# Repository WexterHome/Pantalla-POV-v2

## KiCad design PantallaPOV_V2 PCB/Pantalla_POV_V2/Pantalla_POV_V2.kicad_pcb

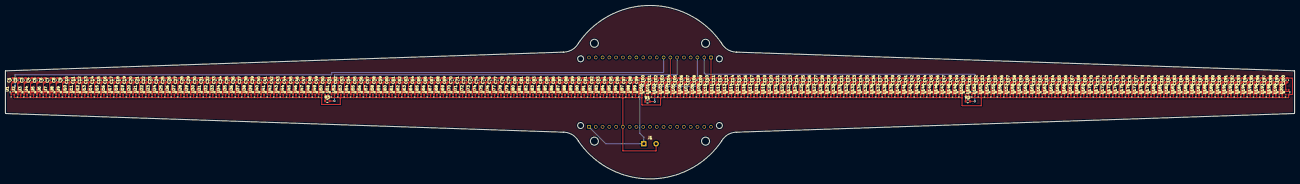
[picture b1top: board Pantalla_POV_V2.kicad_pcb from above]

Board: 2 copper layers, 483.1 x 65.0 mm, 405 parts (1 on the bottom side), 205 nets.

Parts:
C1, C2, C3, C4, C5, C6, C7, C8, C9, C10, C11, C12, C13, C14, C15, C16, C17, C18, C19, C20, C21, C22, C23, C24, C25, C26, C27, C28, C29, C30, C31, C32, C33, C34, C35, C36, C37, C38, C39, C40, C41, C42, C43, C44, C45, C46, C47, C48, C49, C50, C51, C52, C53, C54, C55, C56, C57, C58, C59, C60, C61, C62, C63, C64, C65, C66, C67, C68, C69, C70, C71, C72, C73, C74, C75, C76, C77, C78, C79, C80, C81, C82, C83, C84, C85, C86, C87, C88, C89, C90, C91, C92, C93, C94, C95, C96, C97, C98, C99, C100, C101, C102, C103, C104, C105, C106, C107, C108, C109, C110, C111, C112, C113, C114, C115, C116, C117, C118, C119, C120, C121, C122, C123, C124, C125, C126, C127, C128, C129, C130, C131, C132, C133, C134, C135, C136, C137, C138, C139, C140, C141, C142, C143, C144, C145, C146, C147, C148, C149, C150, C151, C152, C153, C154, C155, C156, C157, C158, C159, C160, C161, C162, C163, C164, C165, C166, C167, C168, C169, C170, C171, C172, C173, C174, C175, C176, C177, C178, C179, C180, C181, C182, C183, C184, C185, C186, C187, C188, C189, C190, C191, C192, C193, C194, C195, C196, C197, C198, C199, C200: C; C_0603_1608Metric
J1: Conn_01x02_Female; SolderWire-0.5sqmm_1x02_P4.6mm_D0.9mm_OD2.1mm
R1, R2, R3: 0; R_0603_1608Metric
U1, U2, U3, U4, U5, U6, U7, U8, U9, U10, U11, U12, U13, U14, U15, U16, U17, U18, U19, U20, U21, U22, U23, U24, U25, U26, U27, U28, U29, U30, U31, U32, U33, U34, U35, U36, U37, U38, U39, U40, U41, U42, U43, U44, U45, U46, U47, U48, U49, U50, U51, U52, U53, U54, U55, U56, U57, U58, U59, U60, U61, U62, U63, U64, U65, U66, U67, U68, U69, U70, U71, U72, U73, U74, U75, U76, U77, U78, U79, U80, U81, U82, U83, U84, U85, U86, U87, U88, U89, U90, U91, U92, U93, U94, U95, U96, U97, U98, U99, U100, U101, U102, U103, U104, U105, U106, U107, U108, U109, U110, U111, U112, U113, U114, U115, U116, U117, U118, U119, U120, U121, U122, U123, U124, U125, U126, U127, U128, U129, U130, U131, U132, U133, U134, U135, U136, U137, U138, U139, U140, U141, U142, U143, U144, U145, U146, U147, U148, U149, U150, U151, U152, U153, U154, U155, U156, U157, U158, U159, U160, U161, U162, U163, U164, U165, U166, U167, U168, U169, U170, U171, U172, U173, U174, U175, U176, U177, U178, U179, U180, U181, U182, U183, U184, U185, U186, U187, U188, U189, U190, U191, U192, U193, U194, U195, U196, U197, U198, U199, U200: WS2812-2020; LED_WS2812-2020
U201: ESP32_NODEMCU; MODULE_ESP32_NODEMCU

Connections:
/FIRST_SECTION_OF_LEDS: U1.3 (DI), U201.J4_8 (G19)
/FOURD_SECTION_OF_LEDS: R2.2, U151.3 (DI), U201.J4_2 (G23)
/LEDS_ROW_1-2: U30.1 (DO), U31.3 (DI)
/LEDS_ROW_2-3: U60.1 (DO), U61.3 (DI)
/LEDS_ROW_3-4: U90.1 (DO), U91.3 (DI)
/LEDS_ROW_4-5: U120.1 (DO), U121.3 (DI)
/LEDS_ROW_5-6: R2.1, U150.1 (DO)
/LEDS_ROW_6-7: U180.1 (DO), U181.3 (DI)
/SECOND_SECTION_OF_LEDS: R3.2, U51.3 (DI), U201.J4_6 (G21)
/THIRD_SECTION_OF_LEDS: R1.2, U101.3 (DI), U201.J4_3 (G22)
GND: C1.2, C2.2, C3.2, C4.2, C5.2, C6.2, C7.2, C8.2, C9.2, C10.2, C11.2, C12.2, C13.2, C14.2, C15.2, C16.2, C17.2, C18.2, C19.2, C20.2, C21.2, C22.2, C23.2, C24.2, C25.2, C26.2, C27.2, C28.2, C29.2, C30.2, C31.2, C32.2, C33.2, C34.2, C35.2, C36.2, C37.2, C38.2, C39.2, C40.2, C41.2, C42.2, C43.2, C44.2, C45.2, C46.2, C47.2, C48.2, C49.2, C50.2, C51.2, C52.2, C53.2, C54.2, C55.2, C56.2, C57.2, C58.2, C59.2, C60.2, C61.2, C62.2, C63.2, C64.2, C65.2, C66.2, C67.2, C68.2, C69.2, C70.2, C71.2, C72.2, C73.2, C74.2, C75.2, C76.2, C77.2, C78.2, C79.2, C80.2, C81.2, C82.2, C83.2, C84.2, C85.2, C86.2, C87.2, C88.2, C89.2, C90.2, C91.2, C92.2, C93.2, C94.2, C95.2, C96.2, C97.2, C98.2, C99.2, C100.2, C101.2, C102.2, C103.2, C104.2, C105.2, C106.2, C107.2, C108.2, C109.2, C110.2, C111.2, C112.2, C113.2, C114.2, C115.2, C116.2, C117.2, C118.2, C119.2, C120.2, C121.2, C122.2, C123.2, C124.2, C125.2, C126.2, C127.2, C128.2, C129.2, C130.2, C131.2, C132.2, C133.2, C134.2, C135.2, C136.2, C137.2, C138.2, C139.2, C140.2, C141.2, C142.2, C143.2, C144.2, C145.2, C146.2, C147.2, C148.2, C149.2, C150.2, C151.2, C152.2, C153.2, C154.2, C155.2, C156.2, C157.2, C158.2, C159.2, C160.2, C161.2, C162.2, C163.2, C164.2, C165.2, C166.2, C167.2, C168.2, C169.2, C170.2, C171.2, C172.2, C173.2, C174.2, C175.2, C176.2, C177.2, C178.2, C179.2, C180.2, C181.2, C182.2, C183.2, C184.2, C185.2, C186.2, C187.2, C188.2, C189.2, C190.2, C191.2, C192.2, C193.2, C194.2, C195.2, C196.2, C197.2, C198.2, C199.2, C200.2, J1.2, U1.2 (GND), U2.2 (GND), U3.2 (GND), U4.2 (GND), U5.2 (GND), U6.2 (GND), U7.2 (GND), U8.2 (GND), U9.2 (GND), U10.2 (GND), U11.2 (GND), U12.2 (GND), U13.2 (GND), U14.2 (GND), U15.2 (GND), U16.2 (GND), U17.2 (GND), U18.2 (GND), U19.2 (GND), U20.2 (GND), U21.2 (GND), U22.2 (GND), U23.2 (GND), U24.2 (GND), U25.2 (GND), U26.2 (GND), U27.2 (GND), U28.2 (GND), U29.2 (GND), U30.2 (GND), U31.2 (GND), U32.2 (GND), U33.2 (GND), U34.2 (GND), U35.2 (GND), U36.2 (GND), U37.2 (GND), U38.2 (GND), U39.2 (GND), U40.2 (GND), U41.2 (GND), U42.2 (GND), U43.2 (GND), U44.2 (GND), U45.2 (GND), U46.2 (GND), U47.2 (GND), U48.2 (GND), U49.2 (GND), U50.2 (GND), U51.2 (GND), U52.2 (GND), U53.2 (GND), U54.2 (GND), U55.2 (GND), U56.2 (GND), U57.2 (GND), U58.2 (GND), U59.2 (GND), U60.2 (GND), U61.2 (GND), U62.2 (GND), U63.2 (GND), U64.2 (GND), U65.2 (GND), U66.2 (GND), U67.2 (GND), U68.2 (GND), U69.2 (GND), U70.2 (GND), U71.2 (GND), U72.2 (GND), U73.2 (GND), U74.2 (GND), U75.2 (GND), U76.2 (GND), U77.2 (GND), U78.2 (GND), U79.2 (GND), U80.2 (GND), U81.2 (GND), U82.2 (GND), U83.2 (GND), U84.2 (GND), U85.2 (GND), U86.2 (GND), U87.2 (GND), U88.2 (GND), U89.2 (GND), U90.2 (GND), U91.2 (GND), U92.2 (GND), U93.2 (GND), U94.2 (GND), U95.2 (GND), U96.2 (GND), U97.2 (GND), U98.2 (GND), U99.2 (GND), U100.2 (GND), U101.2 (GND), U102.2 (GND), U103.2 (GND), U104.2 (GND), U105.2 (GND), U106.2 (GND), U107.2 (GND), U108.2 (GND), U109.2 (GND), U110.2 (GND), U111.2 (GND), U112.2 (GND), U113.2 (GND), U114.2 (GND), U115.2 (GND), U116.2 (GND), U117.2 (GND), U118.2 (GND), U119.2 (GND), U120.2 (GND), U121.2 (GND), U122.2 (GND), U123.2 (GND), U124.2 (GND), U125.2 (GND), U126.2 (GND), U127.2 (GND), U128.2 (GND), U129.2 (GND), U130.2 (GND), U131.2 (GND), U132.2 (GND), U133.2 (GND), U134.2 (GND), U135.2 (GND), U136.2 (GND), U137.2 (GND), U138.2 (GND), U139.2 (GND), U140.2 (GND), U141.2 (GND), U142.2 (GND), U143.2 (GND), U144.2 (GND), U145.2 (GND), U146.2 (GND), U147.2 (GND), U148.2 (GND), U149.2 (GND), U150.2 (GND), U151.2 (GND), U152.2 (GND), U153.2 (GND), U154.2 (GND), U155.2 (GND), U156.2 (GND), U157.2 (GND), U158.2 (GND), U159.2 (GND), U160.2 (GND), U161.2 (GND), U162.2 (GND), U163.2 (GND), U164.2 (GND), U165.2 (GND), U166.2 (GND), U167.2 (GND), U168.2 (GND), U169.2 (GND), U170.2 (GND), U171.2 (GND), U172.2 (GND), U173.2 (GND), U174.2 (GND), U175.2 (GND), U176.2 (GND), U177.2 (GND), U178.2 (GND), U179.2 (GND), U180.2 (GND), U181.2 (GND), U182.2 (GND), U183.2 (GND), U184.2 (GND), U185.2 (GND), U186.2 (GND), U187.2 (GND), U188.2 (GND), U189.2 (GND), U190.2 (GND), U191.2 (GND), U192.2 (GND), U193.2 (GND), U194.2 (GND), U195.2 (GND), U196.2 (GND), U197.2 (GND), U198.2 (GND), U199.2 (GND), U200.2 (GND), U201.J4_1 (GND), U201.J4_7 (GND), U201.J5_6 (GND)
unnamed: R1.1, U100.1 (DO)
unnamed: R3.1, U50.1 (DO)
unnamed: U1.1 (DO), U2.3 (DI)
unnamed: U2.1 (DO), U3.3 (DI)
unnamed: U3.1 (DO), U4.3 (DI)
unnamed: U4.1 (DO), U5.3 (DI)
unnamed: U5.1 (DO), U6.3 (DI)
unnamed: U6.1 (DO), U7.3 (DI)
unnamed: U7.1 (DO), U8.3 (DI)
unnamed: U8.1 (DO), U9.3 (DI)
unnamed: U10.1 (DO), U11.3 (DI)
unnamed: U9.1 (DO), U10.3 (DI)
unnamed: U11.1 (DO), U12.3 (DI)
unnamed: U12.1 (DO), U13.3 (DI)
unnamed: U13.1 (DO), U14.3 (DI)
unnamed: U14.1 (DO), U15.3 (DI)
unnamed: U15.1 (DO), U16.3 (DI)
unnamed: U16.1 (DO), U17.3 (DI)
unnamed: U17.1 (DO), U18.3 (DI)
unnamed: U18.1 (DO), U19.3 (DI)
unnamed: U19.1 (DO), U20.3 (DI)
unnamed: U20.1 (DO), U21.3 (DI)
unnamed: U21.1 (DO), U22.3 (DI)
unnamed: U22.1 (DO), U23.3 (DI)
unnamed: U23.1 (DO), U24.3 (DI)
unnamed: U24.1 (DO), U25.3 (DI)
unnamed: U25.1 (DO), U26.3 (DI)
unnamed: U26.1 (DO), U27.3 (DI)
unnamed: U27.1 (DO), U28.3 (DI)
unnamed: U28.1 (DO), U29.3 (DI)
unnamed: U29.1 (DO), U30.3 (DI)
unnamed: U31.1 (DO), U32.3 (DI)
unnamed: U32.1 (DO), U33.3 (DI)
unnamed: U33.1 (DO), U34.3 (DI)
unnamed: U34.1 (DO), U35.3 (DI)
unnamed: U35.1 (DO), U36.3 (DI)
unnamed: U36.1 (DO), U37.3 (DI)
unnamed: U37.1 (DO), U38.3 (DI)
unnamed: U38.1 (DO), U39.3 (DI)
unnamed: U39.1 (DO), U40.3 (DI)
unnamed: U40.1 (DO), U41.3 (DI)
unnamed: U41.1 (DO), U42.3 (DI)
unnamed: U42.1 (DO), U43.3 (DI)
unnamed: U43.1 (DO), U44.3 (DI)
unnamed: U44.1 (DO), U45.3 (DI)
unnamed: U45.1 (DO), U46.3 (DI)
unnamed: U46.1 (DO), U47.3 (DI)
unnamed: U47.1 (DO), U48.3 (DI)
unnamed: U48.1 (DO), U49.3 (DI)
unnamed: U49.1 (DO), U50.3 (DI)
unnamed: U51.1 (DO), U52.3 (DI)
unnamed: U52.1 (DO), U53.3 (DI)
unnamed: U53.1 (DO), U54.3 (DI)
unnamed: U54.1 (DO), U55.3 (DI)
unnamed: U55.1 (DO), U56.3 (DI)
unnamed: U56.1 (DO), U57.3 (DI)
unnamed: U57.1 (DO), U58.3 (DI)
unnamed: U58.1 (DO), U59.3 (DI)
unnamed: U59.1 (DO), U60.3 (DI)
unnamed: U61.1 (DO), U62.3 (DI)
unnamed: U62.1 (DO), U63.3 (DI)
unnamed: U63.1 (DO), U64.3 (DI)
unnamed: U64.1 (DO), U65.3 (DI)
unnamed: U65.1 (DO), U66.3 (DI)
unnamed: U66.1 (DO), U67.3 (DI)
unnamed: U67.1 (DO), U68.3 (DI)
unnamed: U68.1 (DO), U69.3 (DI)
unnamed: U69.1 (DO), U70.3 (DI)
unnamed: U70.1 (DO), U71.3 (DI)
unnamed: U71.1 (DO), U72.3 (DI)
unnamed: U72.1 (DO), U73.3 (DI)
unnamed: U73.1 (DO), U74.3 (DI)
unnamed: U74.1 (DO), U75.3 (DI)
unnamed: U75.1 (DO), U76.3 (DI)
unnamed: U76.1 (DO), U77.3 (DI)
unnamed: U77.1 (DO), U78.3 (DI)
unnamed: U78.1 (DO), U79.3 (DI)
unnamed: U79.1 (DO), U80.3 (DI)
unnamed: U80.1 (DO), U81.3 (DI)
unnamed: U81.1 (DO), U82.3 (DI)
unnamed: U82.1 (DO), U83.3 (DI)
unnamed: U83.1 (DO), U84.3 (DI)
unnamed: U84.1 (DO), U85.3 (DI)
unnamed: U85.1 (DO), U86.3 (DI)
unnamed: U86.1 (DO), U87.3 (DI)
unnamed: U87.1 (DO), U88.3 (DI)
unnamed: U88.1 (DO), U89.3 (DI)
unnamed: U89.1 (DO), U90.3 (DI)
unnamed: U91.1 (DO), U92.3 (DI)
unnamed: U92.1 (DO), U93.3 (DI)
unnamed: U93.1 (DO), U94.3 (DI)
unnamed: U94.1 (DO), U95.3 (DI)
unnamed: U95.1 (DO), U96.3 (DI)
unnamed: U96.1 (DO), U97.3 (DI)
unnamed: U97.1 (DO), U98.3 (DI)
unnamed: U98.1 (DO), U99.3 (DI)
unnamed: U99.1 (DO), U100.3 (DI)
unnamed: U101.1 (DO), U102.3 (DI)
unnamed: U102.1 (DO), U103.3 (DI)
unnamed: U103.1 (DO), U104.3 (DI)
unnamed: U104.1 (DO), U105.3 (DI)
unnamed: U105.1 (DO), U106.3 (DI)
unnamed: U106.1 (DO), U107.3 (DI)
unnamed: U107.1 (DO), U108.3 (DI)
unnamed: U108.1 (DO), U109.3 (DI)
unnamed: U109.1 (DO), U110.3 (DI)
unnamed: U110.1 (DO), U111.3 (DI)
unnamed: U111.1 (DO), U112.3 (DI)
unnamed: U112.1 (DO), U113.3 (DI)
unnamed: U113.1 (DO), U114.3 (DI)
unnamed: U114.1 (DO), U115.3 (DI)
unnamed: U115.1 (DO), U116.3 (DI)
unnamed: U116.1 (DO), U117.3 (DI)
unnamed: U117.1 (DO), U118.3 (DI)
unnamed: U118.1 (DO), U119.3 (DI)
unnamed: U119.1 (DO), U120.3 (DI)
unnamed: U121.1 (DO), U122.3 (DI)
unnamed: U122.1 (DO), U123.3 (DI)
unnamed: U123.1 (DO), U124.3 (DI)
unnamed: U124.1 (DO), U125.3 (DI)
unnamed: U125.1 (DO), U126.3 (DI)
unnamed: U126.1 (DO), U127.3 (DI)
unnamed: U127.1 (DO), U128.3 (DI)
unnamed: U128.1 (DO), U129.3 (DI)
unnamed: U129.1 (DO), U130.3 (DI)
unnamed: U130.1 (DO), U131.3 (DI)
unnamed: U131.1 (DO), U132.3 (DI)
unnamed: U132.1 (DO), U133.3 (DI)
unnamed: U133.1 (DO), U134.3 (DI)
unnamed: U134.1 (DO), U135.3 (DI)
unnamed: U135.1 (DO), U136.3 (DI)
unnamed: U136.1 (DO), U137.3 (DI)
unnamed: U137.1 (DO), U138.3 (DI)
unnamed: U138.1 (DO), U139.3 (DI)
unnamed: U139.1 (DO), U140.3 (DI)
unnamed: U140.1 (DO), U141.3 (DI)
unnamed: U141.1 (DO), U142.3 (DI)
unnamed: U142.1 (DO), U143.3 (DI)
unnamed: U143.1 (DO), U144.3 (DI)
unnamed: U144.1 (DO), U145.3 (DI)
unnamed: U145.1 (DO), U146.3 (DI)
unnamed: U146.1 (DO), U147.3 (DI)
unnamed: U147.1 (DO), U148.3 (DI)
unnamed: U148.1 (DO), U149.3 (DI)
unnamed: U149.1 (DO), U150.3 (DI)
unnamed: U151.1 (DO), U152.3 (DI)
unnamed: U152.1 (DO), U153.3 (DI)
unnamed: U153.1 (DO), U154.3 (DI)
unnamed: U154.1 (DO), U155.3 (DI)
unnamed: U155.1 (DO), U156.3 (DI)
unnamed: U156.1 (DO), U157.3 (DI)
unnamed: U157.1 (DO), U158.3 (DI)
unnamed: U158.1 (DO), U159.3 (DI)
unnamed: U159.1 (DO), U160.3 (DI)
unnamed: U160.1 (DO), U161.3 (DI)
unnamed: U161.1 (DO), U162.3 (DI)
unnamed: U162.1 (DO), U163.3 (DI)
unnamed: U163.1 (DO), U164.3 (DI)
unnamed: U164.1 (DO), U165.3 (DI)
unnamed: U165.1 (DO), U166.3 (DI)
unnamed: U166.1 (DO), U167.3 (DI)
unnamed: U167.1 (DO), U168.3 (DI)
unnamed: U168.1 (DO), U169.3 (DI)
unnamed: U169.1 (DO), U170.3 (DI)
unnamed: U170.1 (DO), U171.3 (DI)
unnamed: U171.1 (DO), U172.3 (DI)
unnamed: U172.1 (DO), U173.3 (DI)
unnamed: U173.1 (DO), U174.3 (DI)
unnamed: U174.1 (DO), U175.3 (DI)
unnamed: U175.1 (DO), U176.3 (DI)
unnamed: U176.1 (DO), U177.3 (DI)
unnamed: U177.1 (DO), U178.3 (DI)
unnamed: U178.1 (DO), U179.3 (DI)
unnamed: U179.1 (DO), U180.3 (DI)
unnamed: U181.1 (DO), U182.3 (DI)
unnamed: U182.1 (DO), U183.3 (DI)
unnamed: U183.1 (DO), U184.3 (DI)
unnamed: U184.1 (DO), U185.3 (DI)
unnamed: U185.1 (DO), U186.3 (DI)
unnamed: U186.1 (DO), U187.3 (DI)
unnamed: U187.1 (DO), U188.3 (DI)
unnamed: U188.1 (DO), U189.3 (DI)
unnamed: U189.1 (DO), U190.3 (DI)
unnamed: U190.1 (DO), U191.3 (DI)
unnamed: U191.1 (DO), U192.3 (DI)
unnamed: U192.1 (DO), U193.3 (DI)
unnamed: U193.1 (DO), U194.3 (DI)
unnamed: U194.1 (DO), U195.3 (DI)
unnamed: U195.1 (DO), U196.3 (DI)
unnamed: U196.1 (DO), U197.3 (DI)
unnamed: U197.1 (DO), U198.3 (DI)
unnamed: U198.1 (DO), U199.3 (DI)
unnamed: U199.1 (DO), U200.3 (DI)
VCC: C1.1, C2.1, C3.1, C4.1, C5.1, C6.1, C7.1, C8.1, C9.1, C10.1, C11.1, C12.1, C13.1, C14.1, C15.1, C16.1, C17.1, C18.1, C19.1, C20.1, C21.1, C22.1, C23.1, C24.1, C25.1, C26.1, C27.1, C28.1, C29.1, C30.1, C31.1, C32.1, C33.1, C34.1, C35.1, C36.1, C37.1, C38.1, C39.1, C40.1, C41.1, C42.1, C43.1, C44.1, C45.1, C46.1, C47.1, C48.1, C49.1, C50.1, C51.1, C52.1, C53.1, C54.1, C55.1, C56.1, C57.1, C58.1, C59.1, C60.1, C61.1, C62.1, C63.1, C64.1, C65.1, C66.1, C67.1, C68.1, C69.1, C70.1, C71.1, C72.1, C73.1, C74.1, C75.1, C76.1, C77.1, C78.1, C79.1, C80.1, C81.1, C82.1, C83.1, C84.1, C85.1, C86.1, C87.1, C88.1, C89.1, C90.1, C91.1, C92.1, C93.1, C94.1, C95.1, C96.1, C97.1, C98.1, C99.1, C100.1, C101.1, C102.1, C103.1, C104.1, C105.1, C106.1, C107.1, C108.1, C109.1, C110.1, C111.1, C112.1, C113.1, C114.1, C115.1, C116.1, C117.1, C118.1, C119.1, C120.1, C121.1, C122.1, C123.1, C124.1, C125.1, C126.1, C127.1, C128.1, C129.1, C130.1, C131.1, C132.1, C133.1, C134.1, C135.1, C136.1, C137.1, C138.1, C139.1, C140.1, C141.1, C142.1, C143.1, C144.1, C145.1, C146.1, C147.1, C148.1, C149.1, C150.1, C151.1, C152.1, C153.1, C154.1, C155.1, C156.1, C157.1, C158.1, C159.1, C160.1, C161.1, C162.1, C163.1, C164.1, C165.1, C166.1, C167.1, C168.1, C169.1, C170.1, C171.1, C172.1, C173.1, C174.1, C175.1, C176.1, C177.1, C178.1, C179.1, C180.1, C181.1, C182.1, C183.1, C184.1, C185.1, C186.1, C187.1, C188.1, C189.1, C190.1, C191.1, C192.1, C193.1, C194.1, C195.1, C196.1, C197.1, C198.1, C199.1, C200.1, J1.1, U1.4 (VDD), U2.4 (VDD), U3.4 (VDD), U4.4 (VDD), U5.4 (VDD), U6.4 (VDD), U7.4 (VDD), U8.4 (VDD), U9.4 (VDD), U10.4 (VDD), U11.4 (VDD), U12.4 (VDD), U13.4 (VDD), U14.4 (VDD), U15.4 (VDD), U16.4 (VDD), U17.4 (VDD), U18.4 (VDD), U19.4 (VDD), U20.4 (VDD), U21.4 (VDD), U22.4 (VDD), U23.4 (VDD), U24.4 (VDD), U25.4 (VDD), U26.4 (VDD), U27.4 (VDD), U28.4 (VDD), U29.4 (VDD), U30.4 (VDD), U31.4 (VDD), U32.4 (VDD), U33.4 (VDD), U34.4 (VDD), U35.4 (VDD), U36.4 (VDD), U37.4 (VDD), U38.4 (VDD), U39.4 (VDD), U40.4 (VDD), U41.4 (VDD), U42.4 (VDD), U43.4 (VDD), U44.4 (VDD), U45.4 (VDD), U46.4 (VDD), U47.4 (VDD), U48.4 (VDD), U49.4 (VDD), U50.4 (VDD), U51.4 (VDD), U52.4 (VDD), U53.4 (VDD), U54.4 (VDD), U55.4 (VDD), U56.4 (VDD), U57.4 (VDD), U58.4 (VDD), U59.4 (VDD), U60.4 (VDD), U61.4 (VDD), U62.4 (VDD), U63.4 (VDD), U64.4 (VDD), U65.4 (VDD), U66.4 (VDD), U67.4 (VDD), U68.4 (VDD), U69.4 (VDD), U70.4 (VDD), U71.4 (VDD), U72.4 (VDD), U73.4 (VDD), U74.4 (VDD), U75.4 (VDD), U76.4 (VDD), U77.4 (VDD), U78.4 (VDD), U79.4 (VDD), U80.4 (VDD), U81.4 (VDD), U82.4 (VDD), U83.4 (VDD), U84.4 (VDD), U85.4 (VDD), U86.4 (VDD), U87.4 (VDD), U88.4 (VDD), U89.4 (VDD), U90.4 (VDD), U91.4 (VDD), U92.4 (VDD), U93.4 (VDD), U94.4 (VDD), U95.4 (VDD), U96.4 (VDD), U97.4 (VDD), U98.4 (VDD), U99.4 (VDD), U100.4 (VDD), U101.4 (VDD), U102.4 (VDD), U103.4 (VDD), U104.4 (VDD), U105.4 (VDD), U106.4 (VDD), U107.4 (VDD), U108.4 (VDD), U109.4 (VDD), U110.4 (VDD), U111.4 (VDD), U112.4 (VDD), U113.4 (VDD), U114.4 (VDD), U115.4 (VDD), U116.4 (VDD), U117.4 (VDD), U118.4 (VDD), U119.4 (VDD), U120.4 (VDD), U121.4 (VDD), U122.4 (VDD), U123.4 (VDD), U124.4 (VDD), U125.4 (VDD), U126.4 (VDD), U127.4 (VDD), U128.4 (VDD), U129.4 (VDD), U130.4 (VDD), U131.4 (VDD), U132.4 (VDD), U133.4 (VDD), U134.4 (VDD), U135.4 (VDD), U136.4 (VDD), U137.4 (VDD), U138.4 (VDD), U139.4 (VDD), U140.4 (VDD), U141.4 (VDD), U142.4 (VDD), U143.4 (VDD), U144.4 (VDD), U145.4 (VDD), U146.4 (VDD), U147.4 (VDD), U148.4 (VDD), U149.4 (VDD), U150.4 (VDD), U151.4 (VDD), U152.4 (VDD), U153.4 (VDD), U154.4 (VDD), U155.4 (VDD), U156.4 (VDD), U157.4 (VDD), U158.4 (VDD), U159.4 (VDD), U160.4 (VDD), U161.4 (VDD), U162.4 (VDD), U163.4 (VDD), U164.4 (VDD), U165.4 (VDD), U166.4 (VDD), U167.4 (VDD), U168.4 (VDD), U169.4 (VDD), U170.4 (VDD), U171.4 (VDD), U172.4 (VDD), U173.4 (VDD), U174.4 (VDD), U175.4 (VDD), U176.4 (VDD), U177.4 (VDD), U178.4 (VDD), U179.4 (VDD), U180.4 (VDD), U181.4 (VDD), U182.4 (VDD), U183.4 (VDD), U184.4 (VDD), U185.4 (VDD), U186.4 (VDD), U187.4 (VDD), U188.4 (VDD), U189.4 (VDD), U190.4 (VDD), U191.4 (VDD), U192.4 (VDD), U193.4 (VDD), U194.4 (VDD), U195.4 (VDD), U196.4 (VDD), U197.4 (VDD), U198.4 (VDD), U199.4 (VDD), U200.4 (VDD), U201.J5_1 (5V)
